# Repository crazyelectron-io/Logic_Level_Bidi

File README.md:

Logic Level Converter Bidirectional
=========================

[*Logic Level Converter Bi-Directional (BOB-12009)*](https://www.sparkfun.com/products/12009)

This is a bidirectional logic level converter that allows you to communicate between 3.3V and 5V devices, or 2.8V and 1.8V devices.

Repository Contents
-------------------
* **/Hardware** - All Eagle design files (.brd, .sch, .STL)
* **/Production** - Test bed files and production panel files

Documentation
--------------
* **[Hookup Guide](https://learn.sparkfun.com/tutorials/bi-directional-logic-level-converter-hookup-guide)** - Basic hookup guide
* **[SparkFun Fritzing repo](https://github.com/sparkfun/Fritzing_Parts)** - Fritzing diagrams for SparkFun products.

License Information
-------------------
The hardware is released under [Creative Commons Share-alike 3.0](http://creativecommons.org/licenses/by-sa/3.0/).

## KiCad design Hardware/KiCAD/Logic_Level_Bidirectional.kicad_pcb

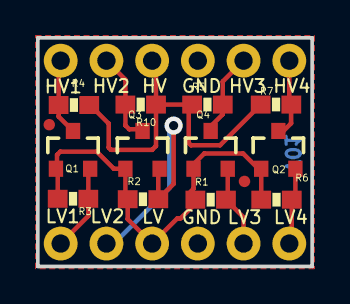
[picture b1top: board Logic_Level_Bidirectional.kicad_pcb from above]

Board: 2 copper layers, 15.2 x 12.7 mm, 18 parts (0 on the bottom side), 10 nets.

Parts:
JP1, JP2: M06SIP; 1X06
JP3, JP4: FIDUCIALUFIDUCIAL; MICRO-FIDUCIAL
LOGO1: SFE_LOGO_FLAME.1_INCH; SFE_LOGO_FLAME_.1
LOGO2: OSHW-LOGOS; OSHW-LOGO-S
Q1, Q2, Q3, Q4: BSS138; SOT23-3
R1, R2, R3, R4, R5, R6, R7, R10: 10K; 0603-RES

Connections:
/GND: JP1.3, JP2.4
/HV1: JP2.1, Q1.3, R4.2
/HV2: JP2.2, Q3.3, R10.2
/HV3: JP2.5, Q4.3, R5.2
/HV4: JP2.6, Q2.3, R7.2
/LV1: JP1.6, Q1.2, R3.2
/LV2: JP1.5, Q3.2, R2.2
/LV3: JP1.2, Q4.2, R1.2
/LV4: JP1.1, Q2.2, R6.2
VCC: JP1.4, JP2.3, Q1.1, Q2.1, Q3.1, Q4.1, R1.1, R2.1, R3.1, R4.1, R5.1, R6.1, R7.1, R10.1
